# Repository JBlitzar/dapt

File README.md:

# dapt

## [Please read] About cost.

So looking at the bom, you can see that it's super expensive, like $50. You might be thinking, "what's going on there? I thought this project was explicitly focused on being low-cost!"

There are a few points I'd like to preempt.

1. I'm not going to spend $50 building this, and if I do so it'll be fine because I can pay out of pocket. That's the BOM for the souped-up set of ALL the adapters in large quantities. I'm going to pick and choose which ones to do, and do it in small quantities. I'm going to end up paying like $15 personally. 
2. There's not really a way to BOM-optimize. Contention genuinely is really high, because LCSC doesn't specialize in THT hobby-solderable components. USB-C SMD genuinely cannot be hand-soldered without a hot plate. If you're trying to make 100 of these, please just buy PCBA and get dirt-cheap SMD components. Right now THT pricing is hit-or-miss. Some are dirt cheap, others are not. 
3. I *could* swap everything out for SMD and order PCBA myself, but at that point it's genuinely a different project. This is what there is. 

## Images

There are no other enclosures, so this is the 3D model too. A STEP export is at `dapt.step`

## What is this project?

dapt is a family of USB adapters. 

There are some opinionated choices that were made:

- Fully passive and chipless. This means that it's just the bare USB protocol: GND, VCC, D+, D-. This also means that you lose out on PD and USB3.0. It's out of scope, but it's what makes this so universal. The only component other than the connectors are some 5.1k resistors that are required for all USB-C to work. 
- tht (for now). This is so that it's hand-solderable.
- just USB. It doesn't try to do too much.

I made dapt because I wanted some dead-simple USB adapters, and I thought it'd be a fun project.

Current adapters:
- A female to A female
- A female to C male
- A male to A male
- A male to C female
- C female to C female
- C female to micro male

## Schematics

| Variant | Schematic |
|---------|-----------|
| A female to A female |  |
| A female to C male |  |
| A male to A male |  |
| A male to C female |  |
| C female to C female |  |
| C female to micro male |  |

## PCB

| Variant | Front | Back |
|---------|-------|------|
| A female to A female |  |  |
| A female to C male |  |  |
| A male to A male |  |  |
| A male to C female |  |  |
| C female to C female |  |  |
| C female to micro male |  |  |

## Production files

in [`PCB/exported_variants/gerbers`](PCB/exported_variants/gerbers). A bit unique because this is multiple boards/variants in one.

## BOM

Please see the *about cost* section.

|Item                     |link                                                                                        |qty|extended price|notes                                          |
|-------------------------|--------------------------------------------------------------------------------------------|---|--------------|-----------------------------------------------|
|C male A female board    |N/A                                                                                         |20 |5.1           |                                               |
|A male A male board      |N/A                                                                                         |5  |4.2           |                                               |
|C female C female board  |N/A                                                                                         |5  |2.1           |                                               |
|A male C female board    |N/A                                                                                         |10 |5.2           |                                               |
|C female micro male board|N/A                                                                                         |10 |5.5           |                                               |
|USB A male               |https://www.lcsc.com/product-detail/C404965.html?s_z=n_q_C404965&globalKeyword=C404965      |15 |1.33          |                                               |
|USB A female             |https://www.lcsc.com/product-detail/C456018.html?s_z=n_q_C456018&globalKeyword=C456018      |20 |0.97          |                                               |
|USB C male               |https://www.lcsc.com/product-detail/C22355747.html?s_z=n_q_C22355747&globalKeyword=C22355747|20 |5.85          |                                               |
|USB C female             |https://www.lcsc.com/product-detail/C22384780.html?s_z=n_q_C22384780&globalKeyword=C22384780|30 |8.53          |                                               |
|micro male               |https://www.lcsc.com/product-detail/C7407276.html?s_z=n_q_C7407276&globalKeyword=C7407276   |10 |11.75         |                                               |
|lcsc + jlc shipping      |N/A                                                                                         |1  |0             |shipping free bc imma order it with other stuff|
|total                    |N/A                                                                                         |1  |50.53         |                                               |

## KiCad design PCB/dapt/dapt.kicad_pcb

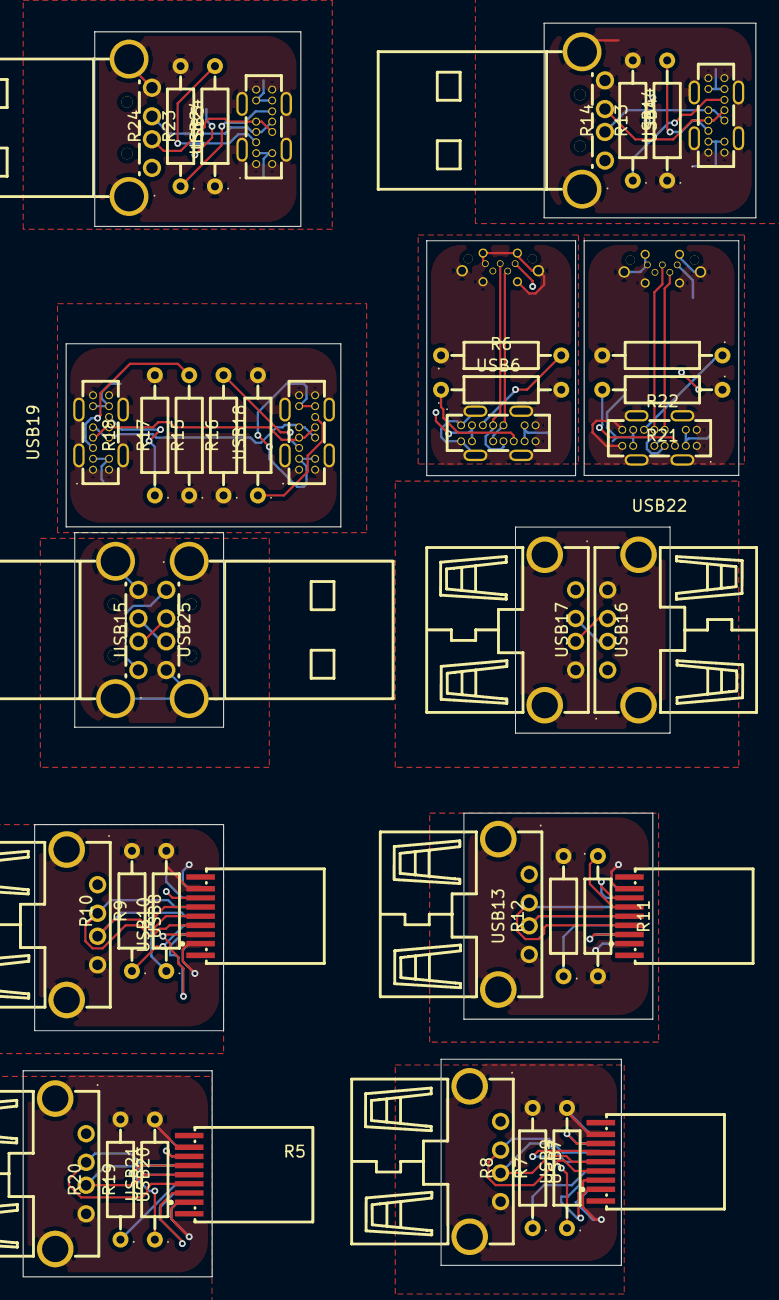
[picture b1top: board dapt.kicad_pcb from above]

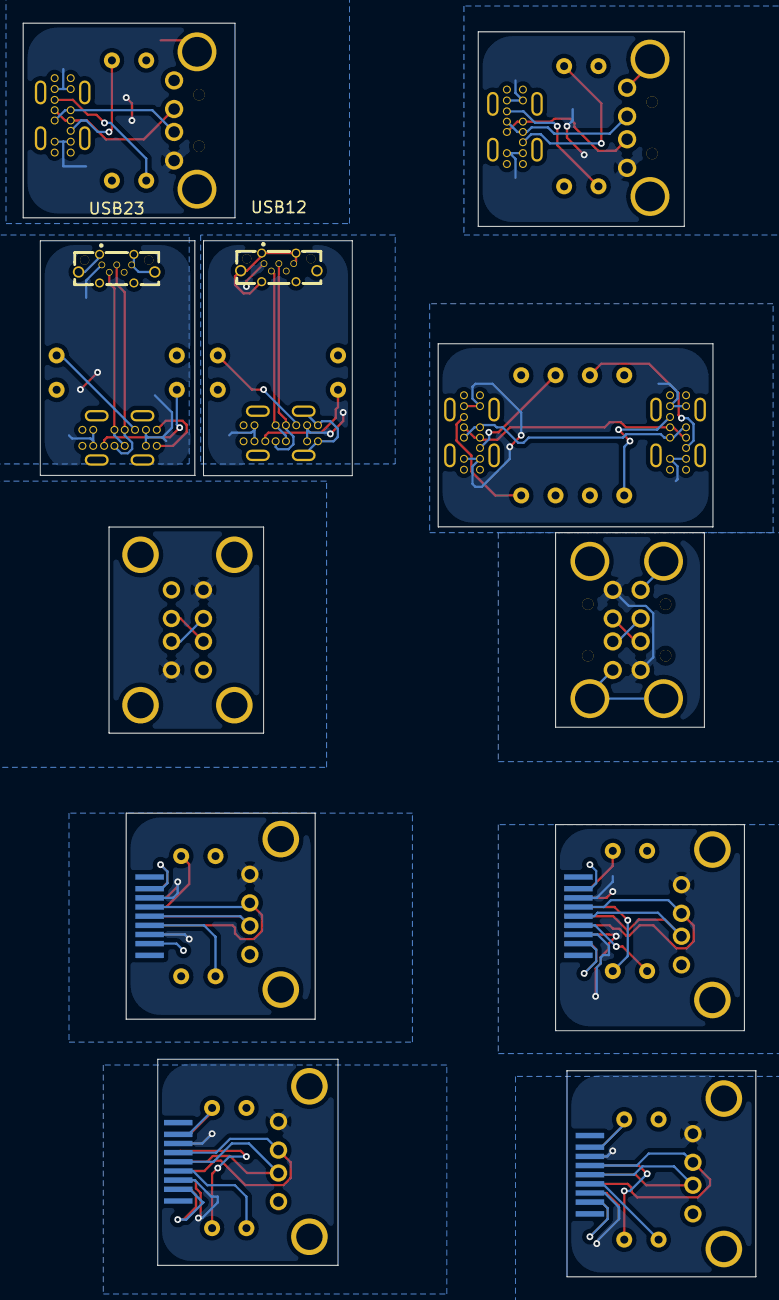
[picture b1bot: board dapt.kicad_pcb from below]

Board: 2 copper layers, 64.0 x 109.5 mm, 42 parts (2 on the bottom side), 64 nets.

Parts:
R5, R6, R7, R8, R9, R10, R11, R12, R13, R14, R15, R16, R17, R18, R19, R20, R21, R22, R23, R24: MF1/4W-5.1KΩ±1%T52; RES-TH_BD2.3-L6.5-P10.50-D0.5
USB4, USB5, USB15, USB25: AM90; USB-AM-TH_AM90
USB6, USB14, USB18, USB19, USB22, USB24: GT-USB-7035A; TYPE-C-TH_GT-USB-7035A
USB7, USB8, USB11, USB20: MC-337; USB-C-SMD_14P-P0.80_MC-337
USB9, USB10, USB13, USB16, USB17, USB21: AF 90° WJDG; USB-A-TH_AF-WJDG
USB12, USB23: USB3150-30-130-A; USB-B-TH_USB3150-30-130-A

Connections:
/A_female_A_female/D+: USB16.3 (D+), USB17.3 (D+)
/A_female_A_female/D-: USB16.2 (D-), USB17.2 (D-)
/A_female_A_female/GND: USB16.4 (GND), USB16.5 (SHLD), USB17.4 (GND), USB17.5 (SHLD)
/A_female_A_female/VBUS: USB16.1 (VCC), USB17.1 (VCC)
/A_female_C_male1/D+: USB8.A6 (Dp1), USB8.B6 (Dp2), USB10.3 (D+)
/A_female_C_male1/D-: USB8.A7 (Dn1), USB8.B7 (Dn2), USB10.2 (D-)
/A_female_C_male1/GND: R9.2, R10.2, USB8.A1 (GND), USB8.A12 (GND), USB8.B1 (GND), USB8.B12 (GND), USB10.4 (GND), USB10.5 (SHLD)
/A_female_C_male1/VBUS: USB8.A4 (VBUS), USB8.A9 (VBUS), USB8.B4 (VBUS), USB8.B9 (VBUS), USB10.1 (VCC)
/A_female_C_male2/D+: USB11.A6 (Dp1), USB11.B6 (Dp2), USB13.3 (D+)
/A_female_C_male2/D-: USB11.A7 (Dn1), USB11.B7 (Dn2), USB13.2 (D-)
/A_female_C_male2/GND: R11.2, R12.2, USB11.A1 (GND), USB11.A12 (GND), USB11.B1 (GND), USB11.B12 (GND), USB13.4 (GND), USB13.5 (SHLD)
/A_female_C_male2/VBUS: USB11.A4 (VBUS), USB11.A9 (VBUS), USB11.B4 (VBUS), USB11.B9 (VBUS), USB13.1 (VCC)
/A_female_C_male3/D+: USB20.A6 (Dp1), USB20.B6 (Dp2), USB21.3 (D+)
/A_female_C_male3/D-: USB20.A7 (Dn1), USB20.B7 (Dn2), USB21.2 (D-)
/A_female_C_male3/GND: R19.2, R20.2, USB20.A1 (GND), USB20.A12 (GND), USB20.B1 (GND), USB20.B12 (GND), USB21.4 (GND), USB21.5 (SHLD)
/A_female_C_male3/VBUS: USB20.A4 (VBUS), USB20.A9 (VBUS), USB20.B4 (VBUS), USB20.B9 (VBUS), USB21.1 (VCC)
/A_female_C_male/D+: USB7.A6 (Dp1), USB7.B6 (Dp2), USB9.3 (D+)
/A_female_C_male/D-: USB7.A7 (Dn1), USB7.B7 (Dn2), USB9.2 (D-)
/A_female_C_male/GND: R7.2, R8.2, USB7.A1 (GND), USB7.A12 (GND), USB7.B1 (GND), USB7.B12 (GND), USB9.4 (GND), USB9.5 (SHLD)
/A_female_C_male/VBUS: USB7.A4 (VBUS), USB7.A9 (VBUS), USB7.B4 (VBUS), USB7.B9 (VBUS), USB9.1 (VCC)
/A_male_A_male/D+: USB15.3 (D+), USB25.3 (D+)
/A_male_A_male/D-: USB15.2 (D-), USB25.2 (D-)
/A_male_A_male/GND: USB15.4 (GND), USB15.MH1, USB15.MH2, USB25.4 (GND), USB25.MH1, USB25.MH2
/A_male_A_male/VBUS: USB15.1 (VCC), USB25.1 (VCC)
/A_male_C_female1/D+: USB5.3 (D+), USB24.A6 (D+), USB24.B6 (D+)
/A_male_C_female1/D-: USB5.2 (D-), USB24.A7 (D-), USB24.B7 (D-)
/A_male_C_female1/GND: R23.1, R24.2, USB5.4 (GND), USB5.MH1, USB5.MH2, USB24.17 (EH), USB24.18 (EH), USB24.19 (EH), USB24.20 (EH), USB24.A1 (GND), USB24.A12 (GND), USB24.B1 (GND), USB24.B12 (GND)
/A_male_C_female1/VBUS: USB5.1 (VCC), USB24.A4 (VBUS), USB24.A9 (VBUS), USB24.B4 (VBUS), USB24.B9 (VBUS)
/A_male_C_female/D+: USB4.3 (D+), USB14.A6 (D+), USB14.B6 (D+)
/A_male_C_female/D-: USB4.2 (D-), USB14.A7 (D-), USB14.B7 (D-)
/A_male_C_female/GND: R13.1, R14.2, USB4.4 (GND), USB4.MH1, USB4.MH2, USB14.17 (EH), USB14.18 (EH), USB14.19 (EH), USB14.20 (EH), USB14.A1 (GND), USB14.A12 (GND), USB14.B1 (GND), USB14.B12 (GND)
/A_male_C_female/VBUS: USB4.1 (VCC), USB14.A4 (VBUS), USB14.A9 (VBUS), USB14.B4 (VBUS), USB14.B9 (VBUS)
/C_female_C_female/D+: USB18.A6 (D+), USB18.B6 (D+), USB19.A6 (D+), USB19.B6 (D+)
/C_female_C_female/D-: USB18.A7 (D-), USB18.B7 (D-), USB19.A7 (D-), USB19.B7 (D-)
/C_female_C_female/GND: R15.1, R16.2, R17.1, R18.2, USB18.17 (EH), USB18.18 (EH), USB18.19 (EH), USB18.20 (EH), USB18.A1 (GND), USB18.A12 (GND), USB18.B1 (GND), USB18.B12 (GND), USB19.17 (EH), USB19.18 (EH), USB19.19 (EH), USB19.20 (EH), USB19.A1 (GND), USB19.A12 (GND), USB19.B1 (GND), USB19.B12 (GND)
/C_female_C_female/VBUS: USB18.A4 (VBUS), USB18.A9 (VBUS), USB18.B4 (VBUS), USB18.B9 (VBUS), USB19.A4 (VBUS), USB19.A9 (VBUS), USB19.B4 (VBUS), USB19.B9 (VBUS)
/C_female_micro_male1/D+: USB22.A6 (D+), USB22.B6 (D+), USB23.3 (D+)
/C_female_micro_male1/D-: USB22.A7 (D-), USB22.B7 (D-), USB23.2 (D-)
/C_female_micro_male1/GND: R21.1, R22.2, USB22.17 (EH), USB22.18 (EH), USB22.19 (EH), USB22.20 (EH), USB22.A1 (GND), USB22.A12 (GND), USB22.B1 (GND), USB22.B12 (GND), USB23.5 (GND), USB23.S1 (EH), USB23.S2 (EH), USB23.S3 (EH), USB23.S4 (EH), USB23.S5 (EH), USB23.S6 (EH)
/C_female_micro_male1/VBUS: USB22.A4 (VBUS), USB22.A9 (VBUS), USB22.B4 (VBUS), USB22.B9 (VBUS), USB23.1 (VBUS)
/C_female_micro_male/D+: USB6.A6 (D+), USB6.B6 (D+), USB12.3 (D+)
/C_female_micro_male/D-: USB6.A7 (D-), USB6.B7 (D-), USB12.2 (D-)
/C_female_micro_male/GND: R5.1, R6.2, USB6.17 (EH), USB6.18 (EH), USB6.19 (EH), USB6.20 (EH), USB6.A1 (GND), USB6.A12 (GND), USB6.B1 (GND), USB6.B12 (GND), USB12.5 (GND), USB12.S1 (EH), USB12.S2 (EH), USB12.S3 (EH), USB12.S4 (EH), USB12.S5 (EH), USB12.S6 (EH)
/C_female_micro_male/VBUS: USB6.A4 (VBUS), USB6.A9 (VBUS), USB6.B4 (VBUS), USB6.B9 (VBUS), USB12.1 (VBUS)
unnamed: R5.2, USB6.A5 (CC1)
unnamed: R6.1, USB6.B5 (CC2)
unnamed: R7.1, USB7.A5 (CC1)
unnamed: R8.1, USB7.B5 (CC2)
unnamed: R9.1, USB8.A5 (CC1)
unnamed: R10.1, USB8.B5 (CC2)
unnamed: R11.1, USB11.A5 (CC1)
unnamed: R12.1, USB11.B5 (CC2)
unnamed: R13.2, USB14.A5 (CC1)
unnamed: R14.1, USB14.B5 (CC2)
unnamed: R15.2, USB18.A5 (CC1)
unnamed: R16.1, USB18.B5 (CC2)
unnamed: R17.2, USB19.A5 (CC1)
unnamed: R18.1, USB19.B5 (CC2)
unnamed: R19.1, USB20.A5 (CC1)
unnamed: R20.1, USB20.B5 (CC2)
unnamed: R21.2, USB22.A5 (CC1)
unnamed: R22.1, USB22.B5 (CC2)
unnamed: R23.2, USB24.A5 (CC1)
unnamed: R24.1, USB24.B5 (CC2)
